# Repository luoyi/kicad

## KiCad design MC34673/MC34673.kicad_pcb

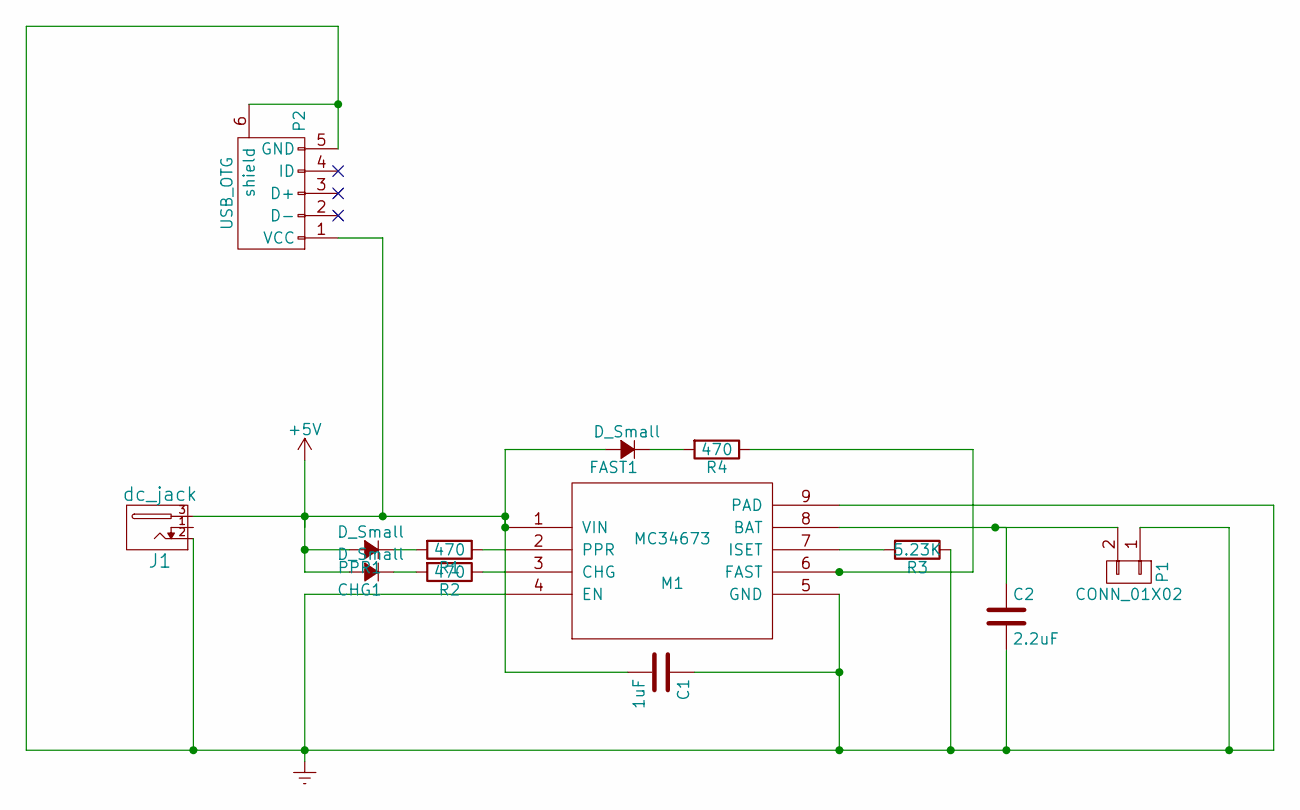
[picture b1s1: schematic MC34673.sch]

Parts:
C1: 1uF; C_0805_HandSoldering
C2: 2.2uF; C_0805_HandSoldering
CHG1: D_Small; LED-3MM
FAST1: D_Small; LED-3MM
J1: dc_jack; dc_socket
M1: MC34673
P1: CONN_01X02; Pin_Header_Straight_1x02
P2: USB_OTG; USB_Micro-B
PPR1: D_Small; LED-3MM
R1, R2, R4: 470; R_0805_HandSoldering
R3: 5.23K; R_0805_HandSoldering

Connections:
+5V: C1.2, CHG1.2 (A), FAST1.2 (A), J1.3, M1.1 (VIN), P2.1 (VCC), PPR1.2 (A)
Earth: C1.1, C2.2, J1.2, M1.4 (EN), M1.5 (GND), M1.9 (PAD), P1.1, P2.5 (GND), P2.6 (shield), R3.1
unnamed: C2.1, M1.8 (BAT), P1.2
unnamed: CHG1.1 (K), R2.2
unnamed: FAST1.1 (K), R4.2
unnamed: M1.2 (PPR), R1.1
unnamed: M1.3 (CHG), R2.1
unnamed: M1.6 (FAST), R4.1
unnamed: M1.7 (ISET), R3.2
unnamed: PPR1.1 (K), R1.2

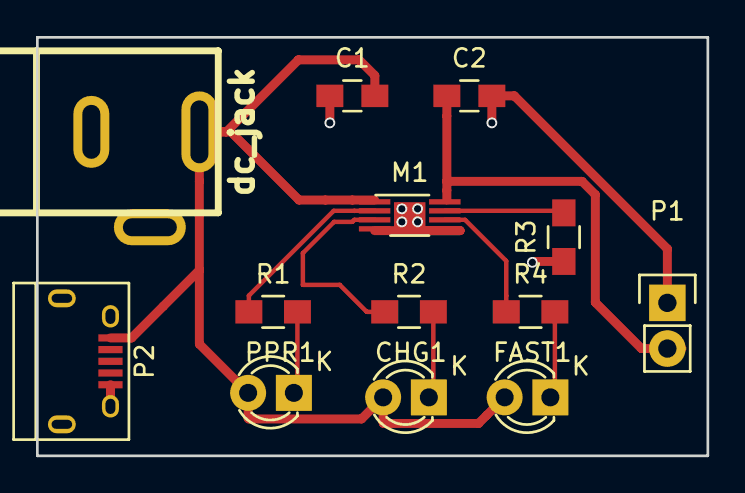
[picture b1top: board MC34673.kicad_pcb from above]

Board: 2 copper layers, 37.2 x 23.2 mm, 13 parts (0 on the bottom side), 10 nets.

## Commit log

2016-08-21 init the kicad project
2016-08-21 add KiCad library file format pdf
2016-08-22 init kilib
2016-08-22 init json support
2016-08-23 support multi def in one library
2016-08-23 add demo
2016-09-06 ready for ickey
